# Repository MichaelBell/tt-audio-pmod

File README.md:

# Tiny Tapeout Audio Pmod

This Pmod is designed to play mono PWM audio from out[7] or bidir[7], while allowing a second Pmod to be plugged in, passing through bidir[0-6] or out[0-6].  

The design has a low pass filter, to allow a large range of audio to be played the cutoff frequency is quite high.  It is therefore recommended that the PWM frequency is at least 200kHz to get good results.

If the piezo is selected with the jumper, it is driven after the low pass filter with no further filtering.

If the headphone jack is selected, AC coupling is applied to give a balanced signal.

The volume trim pot should be turned down to around 30-35 ohms to give nominal line level when the output is connected to a high impedance line in.  If using headphones with a low impedance it should be turned up towards the high end of the range (180-200 ohms).

IO 7 on the second Pmod is pulled high, which allows compatibility with the [QSPI Pmod](https://github.com/mole99/qspi-pmod).

The Pmod was designed in KiCad 8, here is the [schematic](tt-audio-pmod.pdf).

## Example Tiny Tapeout project

This [example project](https://github.com/MichaelBell/tt08-pwm-example) generates a PWM output sampling a sine wave of a configurable frequency.

## Simulation

The frequency response of the design was simulated in ltspice:

The ltspice simulations are in the [sim](sim/) directory.

## Testing

The first version of the Pmod is being manufactured and will be tested soon.

## Credits

Designed for Tiny Tapeout by RebelMike with the help of the excellent Tiny Tapeout Discord community.

   Copyright 2024 Mike Bell

   Licensed under the Apache License, Version 2.0 (the "License");
   you may not use this file except in compliance with the License.
   You may obtain a copy of the License at

   http://www.apache.org/licenses/LICENSE-2.0

   Unless required by applicable law or agreed to in writing, software
   distributed under the License is distributed on an "AS IS" BASIS,
   WITHOUT WARRANTIES OR CONDITIONS OF ANY KIND, either express or implied.
   See the License for the specific language governing permissions and
   limitations under the License.

Image on the reverse is by [ArtRose on Pixabay](https://pixabay.com/vectors/musical-notes-music-smile-merry-6159007/).  Used under the [Pixabay Content License](https://pixabay.com/service/license-summary/)

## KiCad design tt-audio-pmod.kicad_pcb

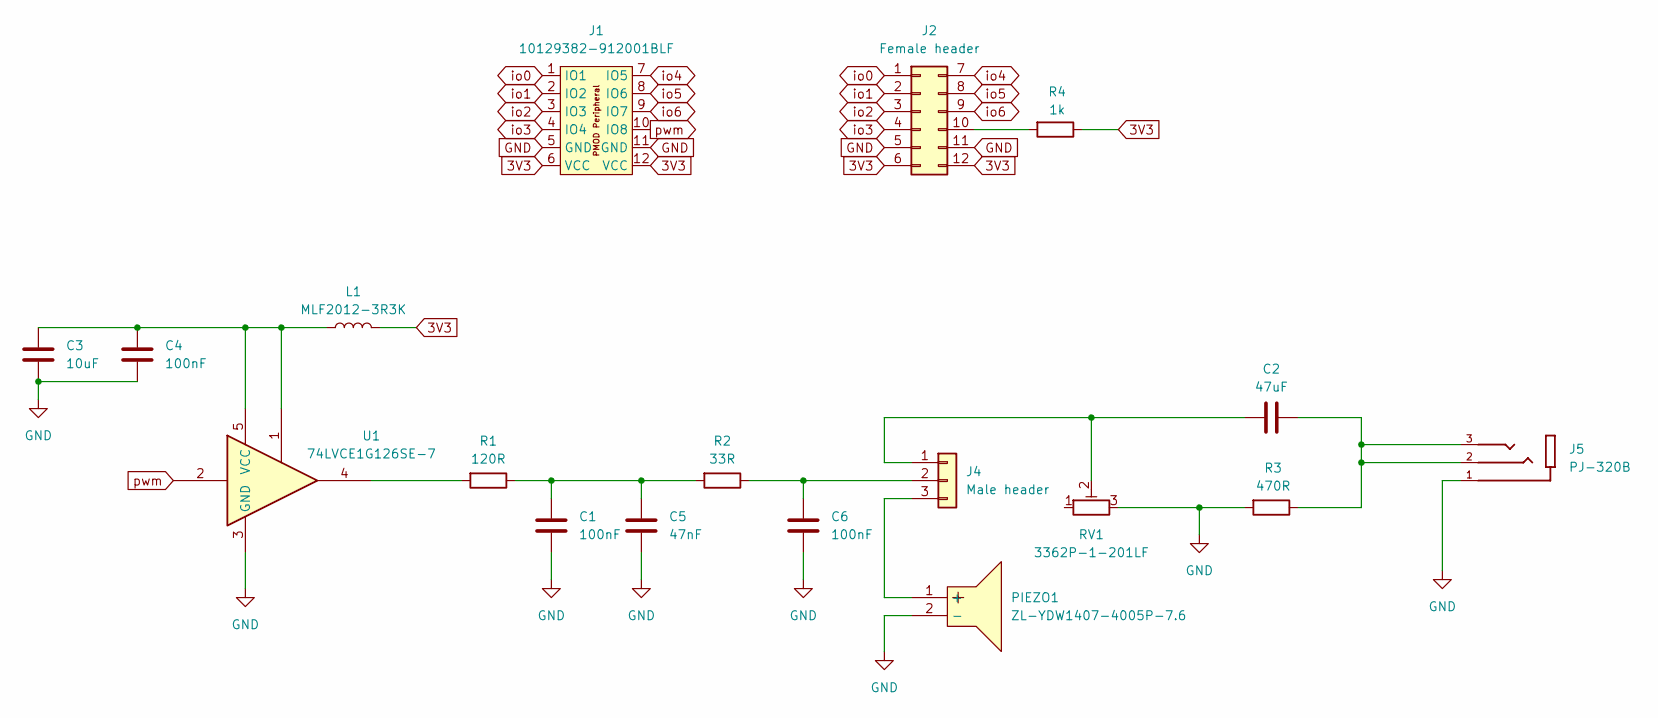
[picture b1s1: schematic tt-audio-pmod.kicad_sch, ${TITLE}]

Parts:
C1, C4, C6: 100nF; C_0603_1608Metric; LCSC Part C14663
C2: 47uF; C_0805_2012Metric; LCSC Part C16780
C3: 10uF; C_0805_2012Metric; LCSC Part C15850
C5: 47nF; C_0603_1608Metric; LCSC Part C1622
J1: 10129382-912001BLF; PinHeader_2x06_P2.54mm_PMODPeriph2B; LCSC Part C60565
J2: Female header; PinSocket_2x06_P2.54mm_Vertical_Column; LCSC Part C92269
J4: Male header; PinHeader_1x03_P2.54mm_Vertical; LCSC Part C49257
J5: PJ-320B; BOOMELE_PJ-320B; LCSC Part C2884998
L1: MLF2012-3R3K; L_0805_2012Metric; LCSC Part C2941578
PIEZO1: ZL-YDW1407-4005P-7.6; BUZ-TH_BD14.0-P7.60-D0.7-FD; LCSC Part C219740
R1: 120R; R_0603_1608Metric; LCSC Part C22787
R2: 33R; R_0603_1608Metric; LCSC Part C23140
R3: 470R; R_0603_1608Metric; LCSC Part C23179
R4: 1k; R_0603_1608Metric; LCSC Part C21190
RV1: 3362P-1-201LF; TRIM_3362P-1-102; LCSC Part C124581
U1: 74LVCE1G126SE-7; SOT-353_SC-70-5; LCSC Part C842506

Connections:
3V3: J1.6 (VCC), J1.12 (VCC), J2.6, J2.12, L1.2, R4.1
GND: C1.2, C3.2, C4.2, C5.2, C6.2, J1.5 (GND), J1.11 (GND), J2.5, J2.11, J5.1, PIEZO1.2 (-), R3.2, RV1.3, U1.3 (GND)
unnamed: C1.1, C5.1, R1.1, R2.2
unnamed: C2.1, J5.2, J5.3, R3.1
unnamed: J2.10, R4.2
unnamed: C2.2, J4.1, RV1.2
unnamed: C6.1, J4.2, R2.1
unnamed: J4.3, PIEZO1.1 (+)
unnamed: R1.2, U1.4
unnamed: C3.1, C4.1, L1.1, U1.1, U1.5 (VCC)
io0: J1.1 (IO1), J2.1
io1: J1.2 (IO2), J2.2
io2: J1.3 (IO3), J2.3
io3: J1.4 (IO4), J2.4
io4: J1.7 (IO5), J2.7
io5: J1.8 (IO6), J2.8
io6: J1.9 (IO7), J2.9
pwm: J1.10 (IO8), U1.2

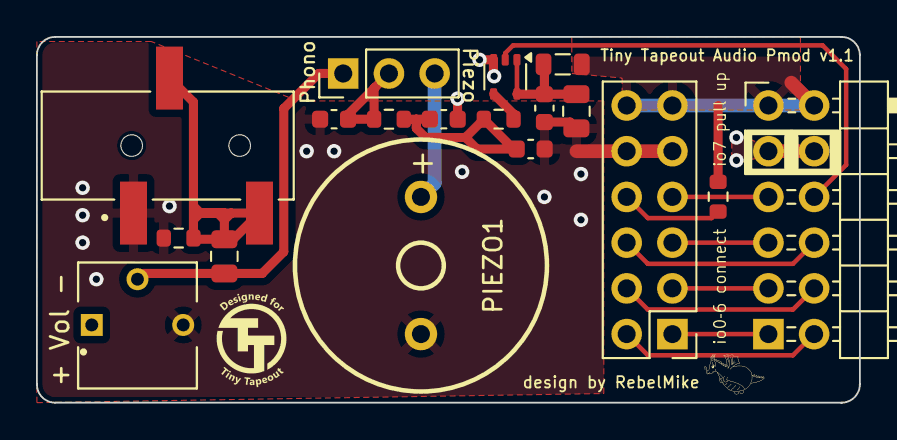
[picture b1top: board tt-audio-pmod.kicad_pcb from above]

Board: 2 copper layers, 45.7 x 20.3 mm, 18 parts (0 on the bottom side), 18 nets.

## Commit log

2024-06-30 Change board shape
2024-07-01 Minor tweaks
2024-07-01 Routed
2024-07-02 Improve ground coherence and thermal relief
2024-07-02 Add art
2024-07-02 Version 1.0 as sent to JLCPCB
2024-07-06 Update Readme, add simulations
2024-07-07 Add link to example project
2024-08-12 Silkscreen and BOM updates
2024-08-12 Remove BOM, instead it will be in release
